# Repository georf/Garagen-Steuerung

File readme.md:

Read here: https://georf.de/1458/garagentor-und-garagen-tool-smart-machen/

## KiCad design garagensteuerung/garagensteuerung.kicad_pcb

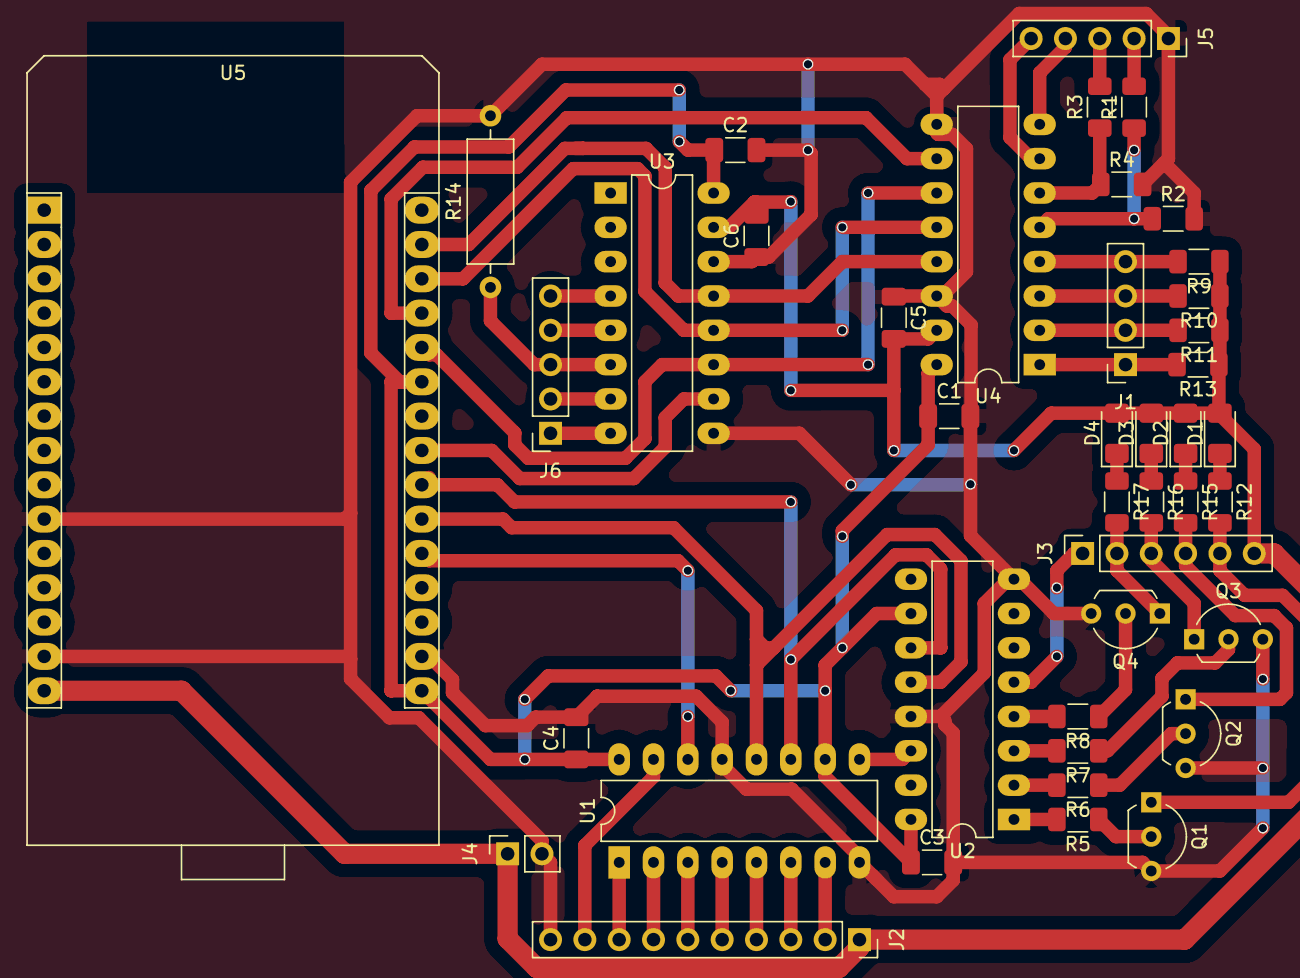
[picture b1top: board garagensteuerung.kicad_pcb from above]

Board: 2 copper layers, 42 parts (0 on the bottom side), 52 nets.

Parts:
C1, C2, C3, C4, C5, C6: 1uF; C_1206_3216Metric_Pad1.33x1.80mm_HandSolder
D1, D2, D3, D4: RED; LED_1206_3216Metric_Pad1.42x1.75mm_HandSolder
J1: Conn_01x04_Female; PinSocket_1x04_P2.54mm_Vertical
J2: Relais-Connector; PinSocket_1x10_P2.54mm_Vertical
J3: Tor-Connector; PinSocket_1x06_P2.54mm_Vertical
J4: Conn_01x02_Female; PinSocket_1x02_P2.54mm_Vertical
J5: Anzeige_Connector; PinSocket_1x05_P2.54mm_Vertical
J6: Sensor_Connector; PinSocket_1x05_P2.54mm_Vertical
Q1, Q2, Q3, Q4: BC547; TO-92L_Inline_Wide
R1, R3: 75k; R_1206_3216Metric_Pad1.30x1.75mm_HandSolder
R2, R4, R5, R6, R7, R8, R9, R10, R11, R13: 15k; R_1206_3216Metric_Pad1.30x1.75mm_HandSolder
R12, R15, R16, R17: 150; R_1206_3216Metric_Pad1.30x1.75mm_HandSolder
R14: 10k; R_Axial_DIN0309_L9.0mm_D3.2mm_P12.70mm_Horizontal
U1, U2: 74HC595; DIP-16_W7.62mm_LongPads
U3, U4: MCP3008; DIP-16_W7.62mm_LongPads
U5: NodeMCU_Amica_R2; node_MCU_ESP8266_longpad

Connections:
+3V3: C1.1, C2.1, C3.1, C4.1, U1.10, U1.16, U2.10, U2.16, U3.16, U4.16, U5.16, U5.25
+5V: C5.2, C6.2, D1.2, D2.2, D3.2, D4.2, J2.1, J3.6, J4.1, R9.1, R10.1, R11.1, R13.1, U3.15, U4.15, U5.15
Anzeige_0: J3.5, Q1.1, R12.2
Anzeige_1: J3.4, Q2.1, R15.2
Anzeige_2: J3.3, Q3.1, R16.2
Anzeige_3: J3.2, Q4.1, R17.2
GND: C1.2, C2.2, C3.2, C4.2, C5.1, C6.1, J2.10, J4.2, J5.1, Q1.3, Q2.3, Q3.3, Q4.3, R2.2, R4.2, R14.2, U1.8, U1.13, U2.8, U2.13, U3.9, U3.14, U4.9, U4.14, U5.10, U5.14, U5.17
Lichtsensor: J6.3, R14.1, U3.6
MISO: U3.12, U4.12, U5.28
MOSI: U3.11, U4.11, U5.26
unnamed: D1.1, R12.1
unnamed: D2.1, R15.1
unnamed: D3.1, R16.1
unnamed: D4.1, R17.1
unnamed: J2.2, U1.7
unnamed: J2.3, U1.6
unnamed: J2.4, U1.5
unnamed: J2.5, U1.4
unnamed: J2.6, U1.3
unnamed: J2.7, U1.2
unnamed: J2.8, U1.1
unnamed: J2.9, U1.15
unnamed: J5.2, R1.2
unnamed: J5.3, R3.2
unnamed: Q1.2, R5.1
unnamed: Q2.2, R6.1
unnamed: Q3.2, R7.1
unnamed: Q4.2, R8.1
unnamed: R5.2, U2.1
unnamed: R6.2, U2.2
unnamed: R7.2, U2.3
unnamed: R8.2, U2.4
unnamed: U1.9, U2.14
SPI_CLK: U3.13, U4.13, U5.29
SPI_CS0: U3.10, U5.23
SPI_CS1: U4.10, U5.27
SRCLK: U1.11, U2.11, U5.22
SRDATA: U1.14, U5.20
SRLOAD: U1.12, U2.12, U5.21
Schalter_1: J1.2, R11.2, U4.2
Schalter_2: J1.1, R13.2, U4.1
Temperatur_0: J6.1, U3.8
Temperatur_1: J6.2, U3.7
TorEndpunkt_0: J5.5, U4.7
TorEndpunkt_1: J5.4, U4.8
TorMotor_0: R1.1, R2.1, U4.5
TorMotor_1: R3.1, R4.1, U4.6
TorTaster: J3.1, U2.5
Tür_0: J1.4, R9.2, U4.4
Tür_1: J1.3, R10.2, U4.3
Unused_0: J6.4, U3.5
Unused_1: J6.5, U3.4

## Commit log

2024-02-11 Version 1
2024-02-11 ignore credentials
2024-02-14 HomeAssistant automatisch anbinden
2024-02-14 Neue Kicad-Version
2024-02-18 Smartgate-Anbindung aktualisieren
2024-02-18 Neustart über MQTT ermöglichen
